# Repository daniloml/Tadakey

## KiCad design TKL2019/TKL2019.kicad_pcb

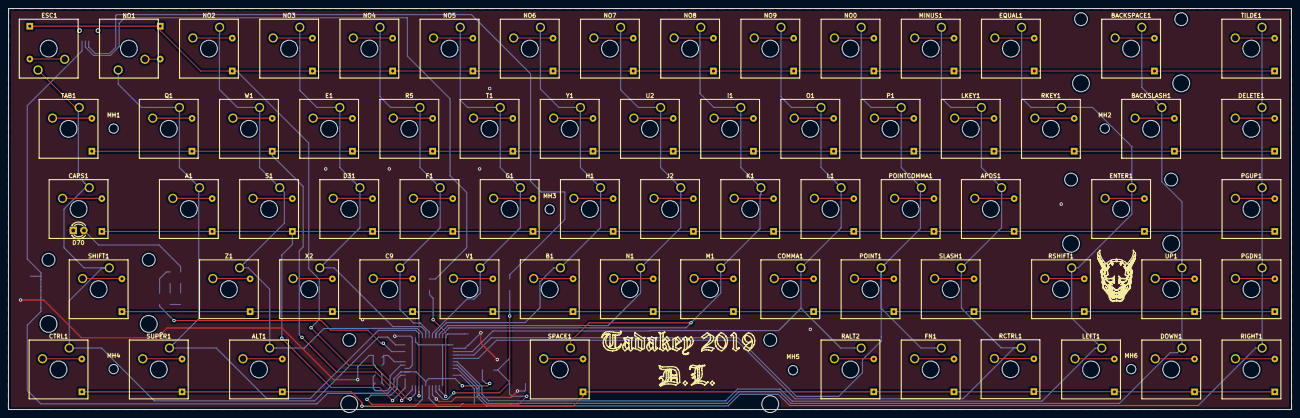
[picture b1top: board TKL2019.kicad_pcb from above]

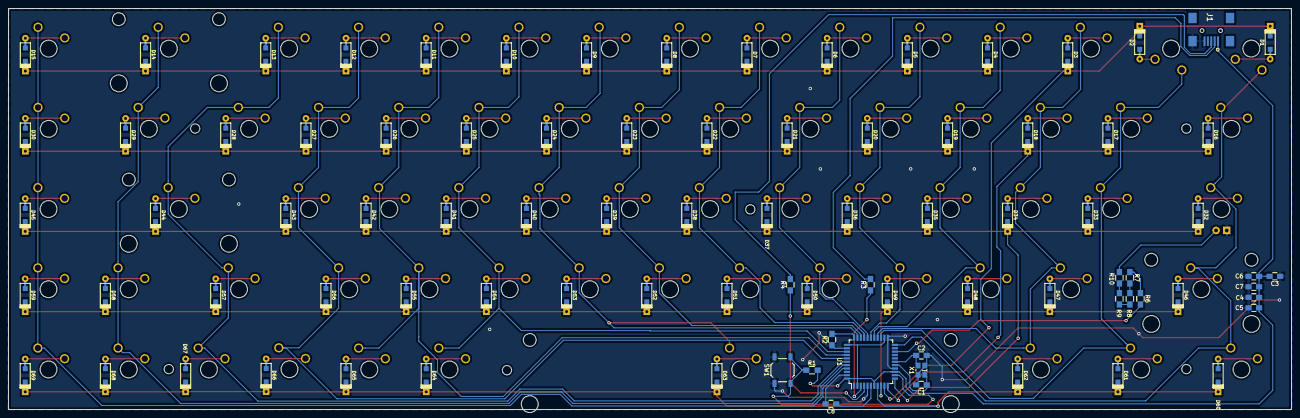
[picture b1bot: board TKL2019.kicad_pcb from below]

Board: 2 copper layers, 304.8 x 95.2 mm, 164 parts (89 on the bottom side), 105 nets.

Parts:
A1: KEYSW; SW_Cherry_MX_1.00u_Plate
ALT1: KEYSW; SW_Cherry_MX_1.25u_Plate
APOS1: KEYSW; SW_Cherry_MX_1.00u_Plate
B1: KEYSW; SW_Cherry_MX_1.00u_Plate
BACKSLASH1: KEYSW; SW_Cherry_MX_1.50u_Plate
BACKSPACE1: KEYSW; SW_Cherry_MX_2.00u_PCB
C1, C2: 22p; C_0805_HandSoldering
C3, C4, C5, C6: 0.1u; C_0805_HandSoldering
C7: 4.7u; C_0805_HandSoldering
C8: 1u; C_0805_HandSoldering
C9: KEYSW; SW_Cherry_MX_1.00u_Plate
CAPS1: KEYSW; SW_Cherry_MX_1.75u_Plate
COMMA1: KEYSW; SW_Cherry_MX_1.00u_Plate
CTRL1: KEYSW; SW_Cherry_MX_1.25u_Plate
D1, D2, D3, D4, D5, D6, D7, D8, D9, D10, D11, D12, D13, D14, D15, D16, D17, D18, D19, D20, D21, D22, D23, D24, D25, D26, D27, D28, D29, D30, D32, D33, D34, D35, D36, D37, D38, D39, D40, D41, D42, D43, D44, D45, D46, D47, D48, D49, D50, D51, D52, D53, D54, D55, D56, D57, D58, D59, D60, D61, D62, D63, D64, D65, D66, D67, D68, D69: D; D_SOD123_axial
D31: KEYSW; SW_Cherry_MX_1.00u_Plate
D70: LED; LED_D3.0mm
DELETE1: KEYSW; SW_Cherry_MX_1.00u_Plate
DOWN1: KEYSW; SW_Cherry_MX_1.00u_Plate
E1: KEYSW; SW_Cherry_MX_1.00u_Plate
ENTER1: KEYSW; SW_Cherry_MX_2.25u_PCB
EQUAL1: KEYSW; SW_Cherry_MX_1.00u_Plate
ESC1: KEYSW; SW_Cherry_MX_1.00u_Plate
F1: KEYSW; SW_Cherry_MX_1.00u_Plate
FN1: KEYSW; SW_Cherry_MX_1.00u_Plate
G1: KEYSW; SW_Cherry_MX_1.00u_Plate
H1: KEYSW; SW_Cherry_MX_1.00u_Plate
I1: KEYSW; SW_Cherry_MX_1.00u_Plate
J1: USB_mini_micro_B; 1734035-2USB
J2: KEYSW; SW_Cherry_MX_1.00u_Plate
K1: KEYSW; SW_Cherry_MX_1.00u_Plate
L1: KEYSW; SW_Cherry_MX_1.00u_Plate
LEFT1: KEYSW; SW_Cherry_MX_1.00u_Plate
LKEY1: KEYSW; SW_Cherry_MX_1.00u_Plate
M1: KEYSW; SW_Cherry_MX_1.00u_Plate
MH1, MH2, MH3, MH4, MH5, MH6: MountingHole_2.2mm_M2
MINUS1: KEYSW; SW_Cherry_MX_1.00u_Plate
N1: KEYSW; SW_Cherry_MX_1.00u_Plate
NO0, NO1, NO2, NO3, NO4, NO5, NO6, NO7, NO8, NO9: KEYSW; SW_Cherry_MX_1.00u_Plate
O1: KEYSW; SW_Cherry_MX_1.00u_Plate
P1: KEYSW; SW_Cherry_MX_1.00u_Plate
PGDN1: KEYSW; SW_Cherry_MX_1.00u_Plate
PGUP1: KEYSW; SW_Cherry_MX_1.00u_Plate
POINT1: KEYSW; SW_Cherry_MX_1.00u_Plate
POINTCOMMA1: KEYSW; SW_Cherry_MX_1.00u_Plate
Q1: KEYSW; SW_Cherry_MX_1.00u_Plate
R1, R2: 10k; R_0805_HandSoldering
R3, R4, R6, R7, R8, R9, R10: 22; R_0805_HandSoldering
R5: KEYSW; SW_Cherry_MX_1.00u_Plate
RALT2: KEYSW; SW_Cherry_MX_1.00u_Plate
RCTRL1: KEYSW; SW_Cherry_MX_1.00u_Plate
RIGHT1: KEYSW; SW_Cherry_MX_1.00u_Plate
RKEY1: KEYSW; SW_Cherry_MX_1.00u_Plate
RSHIFT1: KEYSW; SW_Cherry_MX_1.75u_Plate
S1: KEYSW; SW_Cherry_MX_1.00u_Plate
SHIFT1: KEYSW; SW_Cherry_MX_2.25u_PCB
SLASH1: KEYSW; SW_Cherry_MX_1.00u_Plate
SPACE1: KEYSW; SW_Cherry_MX_6.25u_PCB
SUPER1: KEYSW; SW_Cherry_MX_1.25u_Plate
SW1: SW_PUSH; SW_SPST_TL3342
T1: KEYSW; SW_Cherry_MX_1.00u_Plate
TAB1: KEYSW; SW_Cherry_MX_1.50u_Plate
TILDE1: KEYSW; SW_Cherry_MX_1.00u_Plate
U1: ATMEGA32U4; TQFP-44_10x10mm_P0.8mm
U2: KEYSW; SW_Cherry_MX_1.00u_Plate
UP1: KEYSW; SW_Cherry_MX_1.00u_Plate
V1: KEYSW; SW_Cherry_MX_1.00u_Plate
W1: KEYSW; SW_Cherry_MX_1.00u_Plate
X1: XTAL_GND; crystal_FA238-TSX3225
X2: KEYSW; SW_Cherry_MX_1.00u_Plate
Y1: KEYSW; SW_Cherry_MX_1.00u_Plate
Z1: KEYSW; SW_Cherry_MX_1.00u_Plate

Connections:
/col1: CAPS1.1, CTRL1.1, ESC1.1, SHIFT1.1, TAB1.1, U1.22
/col2: A1.1, NO1.1, Q1.1, SUPER1.1, U1.25
/col3: ALT1.1, NO2.1, S1.1, U1.26, W1.1, Z1.1
/col4: D31.1, E1.1, NO3.1, U1.27, X2.1
/col5: C9.1, F1.1, NO4.1, R5.1, U1.28
/col6: G1.1, NO5.1, T1.1, U1.29, V1.1
/col7: B1.1, H1.1, NO6.1, U1.30, Y1.1
/col8: J2.1, N1.1, NO7.1, U1.31, U2.1
/col9: I1.1, K1.1, M1.1, NO8.1, SPACE1.1, U1.32
/col10: COMMA1.1, L1.1, NO9.1, O1.1, RALT2.1, U1.36
/col11: FN1.1, NO0.1, P1.1, POINT1.1, POINTCOMMA1.1, U1.37
/col12: APOS1.1, LKEY1.1, MINUS1.1, RCTRL1.1, SLASH1.1, U1.38
/col13: ENTER1.1, EQUAL1.1, LEFT1.1, RKEY1.1, RSHIFT1.1, U1.39
/col14: BACKSLASH1.1, BACKSPACE1.1, DOWN1.1, U1.40, UP1.1
/col15: DELETE1.1, PGDN1.1, PGUP1.1, RIGHT1.1, TILDE1.1, U1.41
/row1: D1.1, D2.1, D3.1, D4.1, D5.1, D6.1, D7.1, D8.1, D9.1, D10.1, D11.1, D12.1, D13.1, D14.1, D15.1, U1.10
/row2: D16.1, D17.1, D18.1, D19.1, D20.1, D21.1, D22.1, D23.1, D24.1, D25.1, D26.1, D27.1, D28.1, D29.1, D30.1, U1.11
/row3: D32.1, D33.1, D34.1, D35.1, D36.1, D37.1, D38.1, D39.1, D40.1, D41.1, D42.1, D43.1, D44.1, D45.1, U1.12
/row4: D46.1, D47.1, D48.1, D49.1, D50.1, D51.1, D52.1, D53.1, D54.1, D55.1, D56.1, D57.1, D58.1, D59.1, U1.9
/row5: D60.1, D61.1, D62.1, D63.1, D64.1, D65.1, D66.1, D67.1, D68.1, D69.1, U1.8
GND: C1.2, C2.2, C3.1, C4.1, C5.1, C6.1, C7.1, C8.2, D70.1, J1.5, J1.6, R2.1, SW1.1, U1.5, U1.15, U1.23, U1.35, U1.43, X1.3
unnamed: A1.2, D33.2
unnamed: ALT1.2, D62.2
unnamed: APOS1.2, D43.2
unnamed: B1.2, D51.2
unnamed: BACKSLASH1.2, D29.2
unnamed: BACKSPACE1.2, D14.2
unnamed: C1.1, U1.16, X1.1
unnamed: C2.1, U1.17, X1.2
unnamed: C8.1, U1.6
unnamed: C9.2, D49.2
unnamed: CAPS1.2, D32.2
unnamed: COMMA1.2, D54.2
unnamed: CTRL1.2, D60.2
unnamed: D1.2, ESC1.2
unnamed: D2.2, NO1.2
unnamed: D3.2, NO2.2
unnamed: D4.2, NO3.2
unnamed: D5.2, NO4.2
unnamed: D6.2, NO5.2
unnamed: D7.2, NO6.2
unnamed: D8.2, NO7.2
unnamed: D9.2, NO8.2
unnamed: D10.2, NO9.2
unnamed: D11.2, NO0.2
unnamed: D12.2, MINUS1.2
unnamed: D13.2, EQUAL1.2
unnamed: D15.2, TILDE1.2
unnamed: D16.2, TAB1.2
unnamed: D17.2, Q1.2
unnamed: D18.2, W1.2
unnamed: D19.2, E1.2
unnamed: D20.2, R5.2
unnamed: D21.2, T1.2
unnamed: D22.2, Y1.2
unnamed: D23.2, U2.2
unnamed: D24.2, I1.2
unnamed: D25.2, O1.2
unnamed: D26.2, P1.2
unnamed: D27.2, LKEY1.2
unnamed: D28.2, RKEY1.2
unnamed: D30.2, DELETE1.2
unnamed: D31.2, D35.2
unnamed: D34.2, S1.2
unnamed: D36.2, F1.2
unnamed: D37.2, G1.2
unnamed: D38.2, H1.2
unnamed: D39.2, J2.2
unnamed: D40.2, K1.2
unnamed: D41.2, L1.2
unnamed: D42.2, POINTCOMMA1.2
unnamed: D44.2, ENTER1.2
unnamed: D45.2, PGUP1.2
unnamed: D46.2, SHIFT1.2
unnamed: D47.2, Z1.2
unnamed: D48.2, X2.2
unnamed: D50.2, V1.2
unnamed: D52.2, N1.2
unnamed: D53.2, M1.2
unnamed: D55.2, POINT1.2
unnamed: D56.2, SLASH1.2
unnamed: D57.2, RSHIFT1.2
unnamed: D58.2, UP1.2
unnamed: D59.2, PGDN1.2
unnamed: D61.2, SUPER1.2
unnamed: D63.2, SPACE1.2
unnamed: D64.2, RALT2.2
unnamed: D65.2, FN1.2
unnamed: D66.2, RCTRL1.2
unnamed: D67.2, LEFT1.2
unnamed: D68.2, DOWN1.2
unnamed: D69.2, RIGHT1.2
unnamed: D70.2, R10.1
unnamed: J1.2, R3.2
unnamed: J1.3, R4.2
unnamed: R1.1, SW1.2, U1.13
unnamed: R2.2, U1.33
unnamed: R3.1, U1.3
unnamed: R4.1, U1.4
unnamed: R6.1, U1.20
unnamed: R6.2, R7.1
unnamed: R7.2, R8.1
unnamed: R8.2, R9.2
unnamed: R9.1, R10.2
VCC: C3.2, C4.2, C5.2, C6.2, C7.2, J1.1, R1.2, U1.2, U1.7, U1.14, U1.24, U1.34, U1.44

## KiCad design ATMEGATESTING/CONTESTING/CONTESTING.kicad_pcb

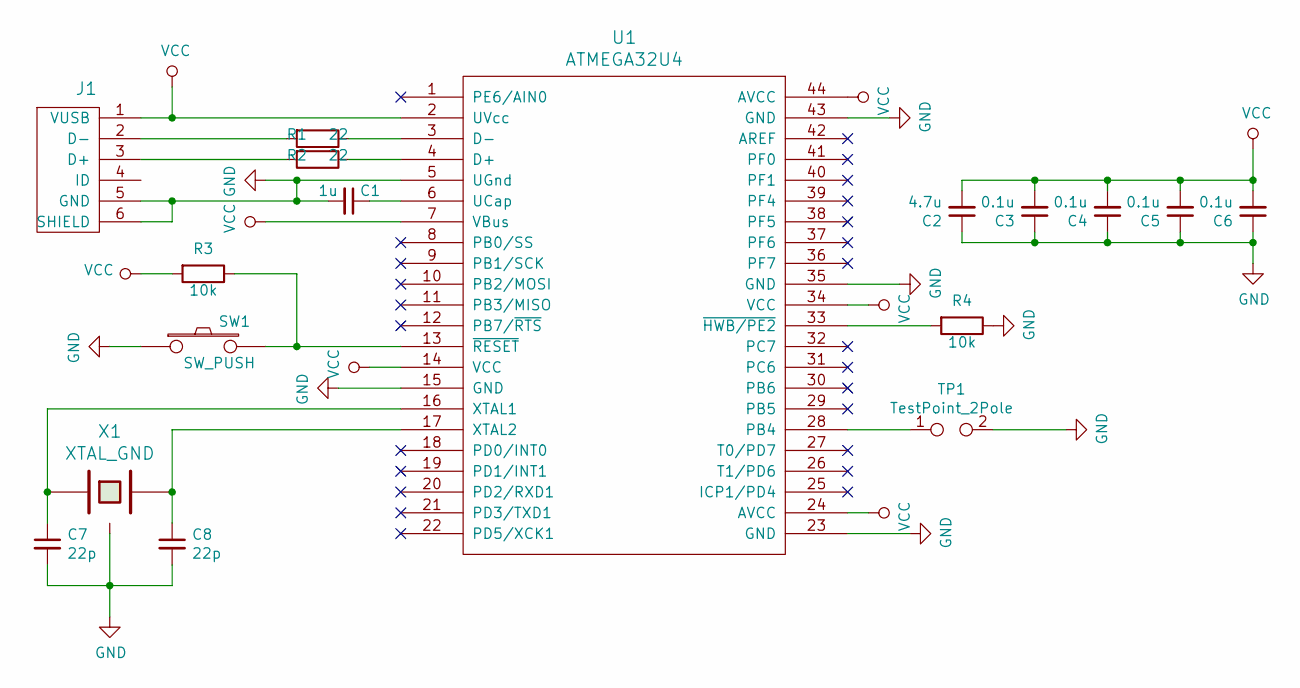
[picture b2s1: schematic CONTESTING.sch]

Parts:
C1: 1u; C_0805_HandSoldering
C2: 4.7u; C_0805_HandSoldering
C3, C4, C5, C6: 0.1u; C_0805_HandSoldering
C7, C8: 22p; C_0805_HandSoldering
J1: USB_mini_micro_B; 1734035-2USB
R1, R2: 22; R_0805_HandSoldering
R3, R4: 10k; R_0805_HandSoldering
SW1: SW_PUSH; SW_SPST_TL3342
TP1: TestPoint_2Pole; Banana_Jack_2Pin
U1: ATMEGA32U4; TQFP-44_10x10mm_P0.8mm
X1: XTAL_GND; crystal_FA238-TSX3225

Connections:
GND: C1.2, C2.1, C3.1, C4.1, C5.1, C6.1, C7.2, C8.2, J1.5 (GND), J1.6 (SHIELD), R4.1, SW1.1, TP1.2, U1.5 (UGnd), U1.15 (GND), U1.23 (GND), U1.35 (GND), U1.43 (GND), X1.3
unnamed: C1.1, U1.6 (UCap)
unnamed: C7.1, U1.16 (XTAL1), X1.1
unnamed: C8.1, U1.17 (XTAL2), X1.2
unnamed: J1.2 (D-), R1.2
unnamed: J1.3 (D+), R2.2
unnamed: R1.1, U1.3 (D-)
unnamed: R2.1, U1.4 (D+)
unnamed: R3.1, SW1.2, U1.13 (~RESET)
unnamed: R4.2, U1.33 (~HWB/PE2)
unnamed: TP1.1, U1.28 (PB4)
VCC: C2.2, C3.2, C4.2, C5.2, C6.2, J1.1 (VUSB), R3.2, U1.2 (UVcc), U1.7 (VBus), U1.14 (VCC), U1.24 (AVCC), U1.34 (VCC), U1.44 (AVCC)

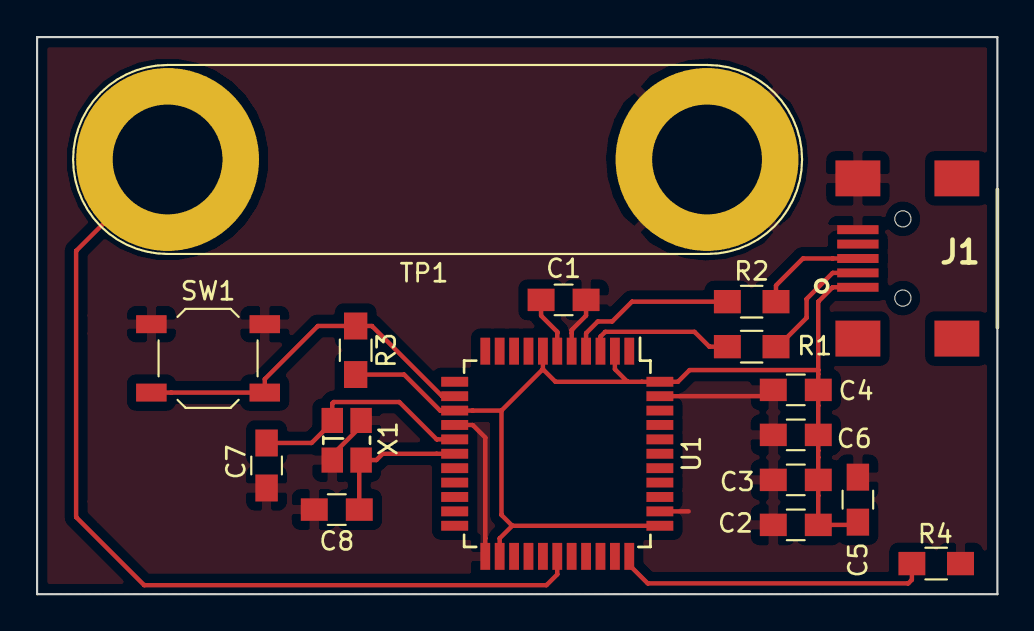
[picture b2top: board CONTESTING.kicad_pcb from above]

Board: 2 copper layers, 53.3 x 31.0 mm, 17 parts (0 on the bottom side), 12 nets.

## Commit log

2019-11-12 some footprints added
2019-12-25 sum progress
2020-01-01 a lot of progress
2020-01-05 changed some stuff
2020-01-12 commit de fin de semana
2020-02-15 bruh
2020-02-15 why dis aint working AAAAAAAAAAAAAAA
2020-03-08 wow epic commit
2020-03-13 fixed dead schematic
